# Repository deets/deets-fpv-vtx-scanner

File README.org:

* VTX Band Scanner

This little project provides a small scanner for the 39 VTX 
bands usually used (not the low L-band).

** Channel Table

| Frequency | Aomway | TBS Unify | Channel |
|-----------+--------+-----------+---------|
|      5645 | A4     | E4        |       0 |
|      5658 | E1     | R1        |       1 |
|      5665 | A3     | E3        |       2 |
|      5685 | A2     | E2        |       3 |
|      5695 | E2     | R2        |       4 |
|      5705 | A1     | E1        |       5 |
|      5725 | C1     | A8        |       6 |
|      5732 | E3     | R3        |       7 |
|      5733 | B1     | B1        |       8 |
|      5740 | D1     | F1        |       9 |
|      5745 | C2     | A7        |      10 |
|      5752 | B2     | B2        |      11 |
|      5760 | D2     | F2        |      12 |
|      5765 | C3     | A6        |      13 |
|      5769 | E4     | R4        |      14 |
|      5771 | B3     | B3        |      15 |
|      5780 | D3     | F3        |      16 |
|      5785 | C4     | A5        |      17 |
|      5790 | B4     | B4        |      18 |
|      5800 | D4     | F4        |      19 |
|      5805 | C5     | A4        |      20 |
|      5806 | E5     | R5        |      21 |
|      5809 | B5     | B5        |      22 |
|      5820 | D5     | F5        |      23 |
|      5825 | C6     | A3        |      24 |
|      5828 | B6     | B6        |      25 |
|      5840 | D6     | F6        |      26 |
|      5843 | E6     | R6        |      27 |
|      5845 | C7     | A2        |      28 |
|      5847 | B7     | B7        |      29 |
|      5860 | D7     | F7        |      30 |
|      5865 | C8     | A1        |      31 |
|      5866 | B8     | B8        |      32 |
|      5880 | D8     | F8        |      33 |
|      5880 | E7     | R7        |      34 |
|      5885 | A5     | E5        |      35 |
|      5905 | A6     | E6        |      36 |
|      5917 | E8     | R8        |      37 |
|      5925 | A7     | E7        |      38 |
|      5945 | A8     | E8        |      39 |
|-----------+--------+-----------+---------|

** RX5808 Connections

|-----+----------|
| Pin | Function |
|-----+----------|
|   1 | CH1/MOSI |
|   2 | CH2/CS   |
|   3 | CH3/CLK  |
|   4 | GND      |
|   5 | 5V       |
|   6 | RSSI     |
|   7 | Audio    |
|   8 | Video    |
|   9 | GND      |
|-----+----------|

** Developing on iOS

*** Dependencies

They are tracked in =Dependencies/Package.swift=.

Add a new =.package=-Declaration, refer it in
=.target(name="Dependencies")= and then run

#+begin_src bash
$ swift package update
$ rake xcodeproj
#+end_src

Then drag the new dependencies into Xcode.

[[https://github.com/apple/swift-package-manager/blob/master/Documentation/PackageDescriptionV4.md][Some explanation about Package.swift]]

*** Core Bluetooth Notes

 - [[https://stackoverflow.com/questions/13286487/how-can-i-reconnect-to-device-after-disconnecting-in-core-bluetooth][Reconnecting BT peripheral.]]

** Credits and Acknowledegements

 - Icons made by [[https://www.flaticon.com/packs/interface/2][Chanut]] from [[https://www.flaticon.com/][Flaticon]] is licensed by [[http://creativecommons.org/licenses/by/3.0/http://creativecommons.org/licenses/by/3.0/][CC 3.0 BY]]

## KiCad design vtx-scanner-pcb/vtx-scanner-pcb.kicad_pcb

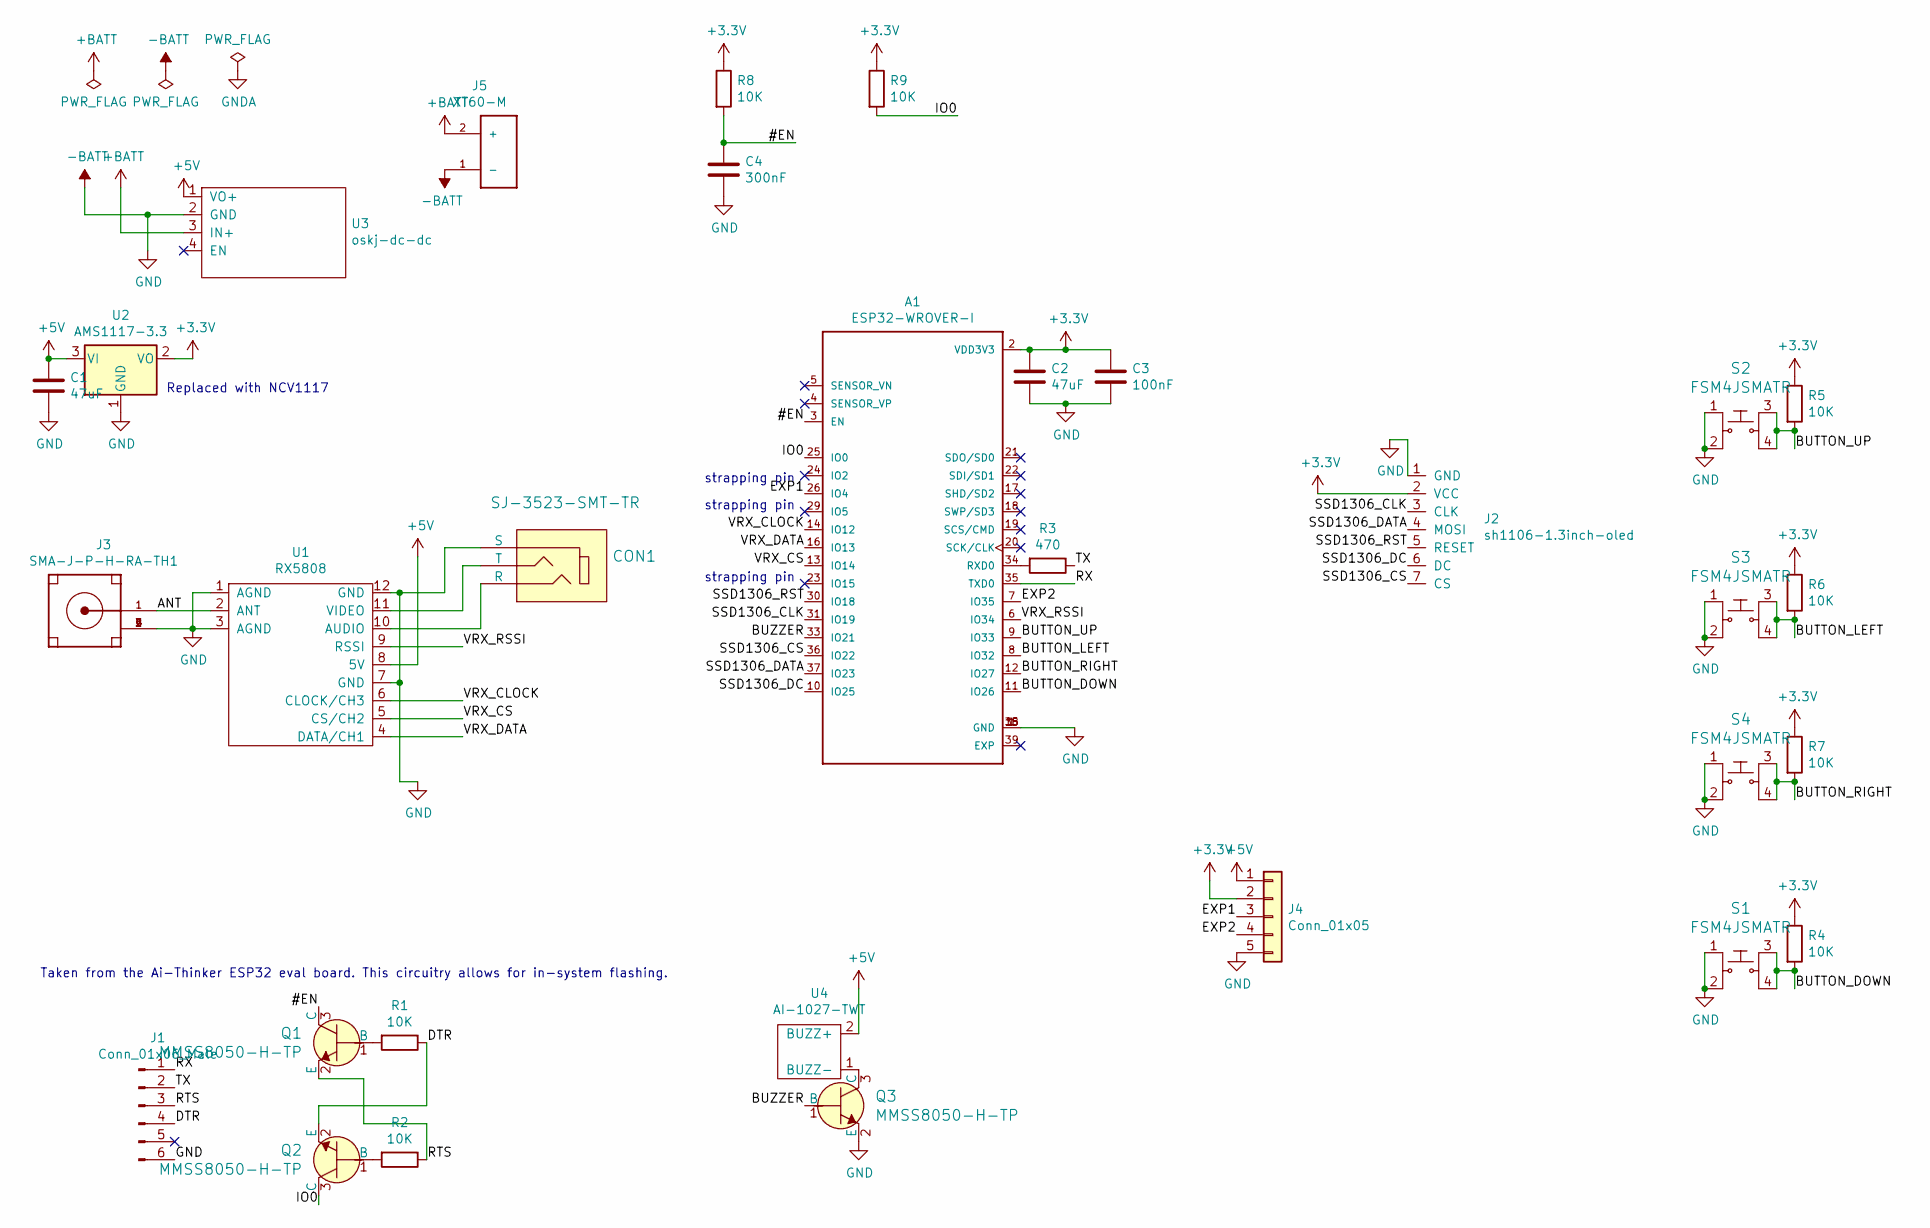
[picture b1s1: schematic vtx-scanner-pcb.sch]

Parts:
A1: ESP32-WROVER-I; XCVR_ESP32-WROVER-I
C1, C2: 47uF; CP_Elec_5x5.8
C3: 100nF; C_0805_2012Metric_Pad1.15x1.40mm_HandSolder
C4: 300nF; C_0805_2012Metric_Pad1.15x1.40mm_HandSolder
CON1: SJ-3523-SMT-TR; Switch_Slide_11.6x4mm_SJ-3523-SMT; MPN SJ-3523-SMT-TR; Digi-Key_PN CP-3523SJCT-ND
J1: Conn_01x06_Male; PinHeader_1x06_P2.54mm_Vertical
J2: sh1106-1.3inch-oled
J3: SMA-J-P-H-RA-TH1; SAMTEC_SMA-J-P-H-RA-TH1
J4: Conn_01x05; JST_PH_S5B-PH-K_1x05_P2.00mm_Horizontal
J5: XT60-M; AMASS_XT60-M-SIDE-MOUNT
Q1, Q2, Q3: MMSS8050-H-TP; SOT-23-3; MPN MMSS8050-H-TP; Digi-Key_PN MMSS8050-H-TPMSCT-ND
R1, R2, R4, R5, R6, R7, R8, R9: 10K; R_1206_3216Metric_Pad1.42x1.75mm_HandSolder
R3: 470; R_1206_3216Metric_Pad1.42x1.75mm_HandSolder
S1, S2, S3, S4: FSM4JSMATR; Switch_Tactile_SMD_6x6mm; MPN FSM4JSMATR; Digi-Key_PN 450-1759-1-ND
U1: RX5808
U2: AMS1117-3.3; SOT-223-3_TabPin2
U3: oskj-dc-dc
U4: AI-1027-TWT

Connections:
+3V3: A1.2 (VDD3V3), C2.1, C3.1, J2.2 (VCC), J4.2, R4.1, R5.1, R6.1, R7.1, R8.1, R9.1, U2.2 (VO)
+5V: C1.1, J4.1, U1.8 (5V), U2.3 (VI), U3.1 (VO+), U4.2 (BUZZ+)
+BATT: J5.2 (+), U3.3 (IN+)
-BATT: A1.1 (GND), A1.15 (GND), A1.38 (GND), C1.2, C2.2, C3.2, C4.2, CON1.1 (S), J1.6, J2.1 (GND), J3.2 (GND), J3.3 (GND), J3.4 (GND), J3.5 (GND), J4.5, J5.1 (-), Q3.2 (E), S1.1, S1.2, S2.1, S2.2, S3.1, S3.2, S4.1, S4.2, U1.1 (AGND), U1.3 (AGND), U1.7 (GND), U1.12 (GND), U2.1 (GND), U3.2 (GND)
/#EN: A1.3 (EN), C4.1, Q1.3 (C), R8.2
/ANT: J3.1 (SIGNAL), U1.2 (ANT)
/BUTTON_DOWN: A1.11 (IO26), R4.2, S1.3, S1.4
/BUTTON_LEFT: A1.8 (IO32), R6.2, S3.3, S3.4
/BUTTON_RIGHT: A1.12 (IO27), R7.2, S4.3, S4.4
/BUTTON_UP: A1.9 (IO33), R5.2, S2.3, S2.4
/BUZZER: A1.33 (IO21), Q3.1 (B)
/DTR: J1.4, Q2.2 (E), R1.1
/EXP1: A1.26 (IO4), J4.3
/EXP2: A1.7 (IO35), J4.4
/IO0: A1.25 (IO0), Q2.3 (C), R9.2
/RTS: J1.3, Q1.2 (E), R2.1
/RX: A1.35 (TXD0), J1.1
/SSD1306_CLK: A1.31 (IO19), J2.3 (CLK)
/SSD1306_CS: A1.36 (IO22), J2.7 (CS)
/SSD1306_DATA: A1.37 (IO23), J2.4 (MOSI)
/SSD1306_DC: A1.10 (IO25), J2.6 (DC)
/SSD1306_RST: A1.30 (IO18), J2.5 (RESET)
/TX: J1.2, R3.1
/VRX_CLOCK: A1.14 (IO12), U1.6 (CLOCK/CH3)
/VRX_CS: A1.13 (IO14), U1.5 (CS/CH2)
/VRX_DATA: A1.16 (IO13), U1.4 (DATA/CH1)
/VRX_RSSI: A1.6 (IO34), U1.9 (RSSI)
unnamed: A1.34 (RXD0), R3.2
unnamed: CON1.2 (T), U1.11 (VIDEO)
unnamed: CON1.3 (R), U1.10 (AUDIO)
unnamed: Q1.1 (B), R1.2
unnamed: Q2.1 (B), R2.2
unnamed: Q3.3 (C), U4.1 (BUZZ-)

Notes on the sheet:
Taken from the Ai-Thinker ESP32 eval board. This circuitry allows for in-system flashing.
strapping pin
Replaced with NCV1117

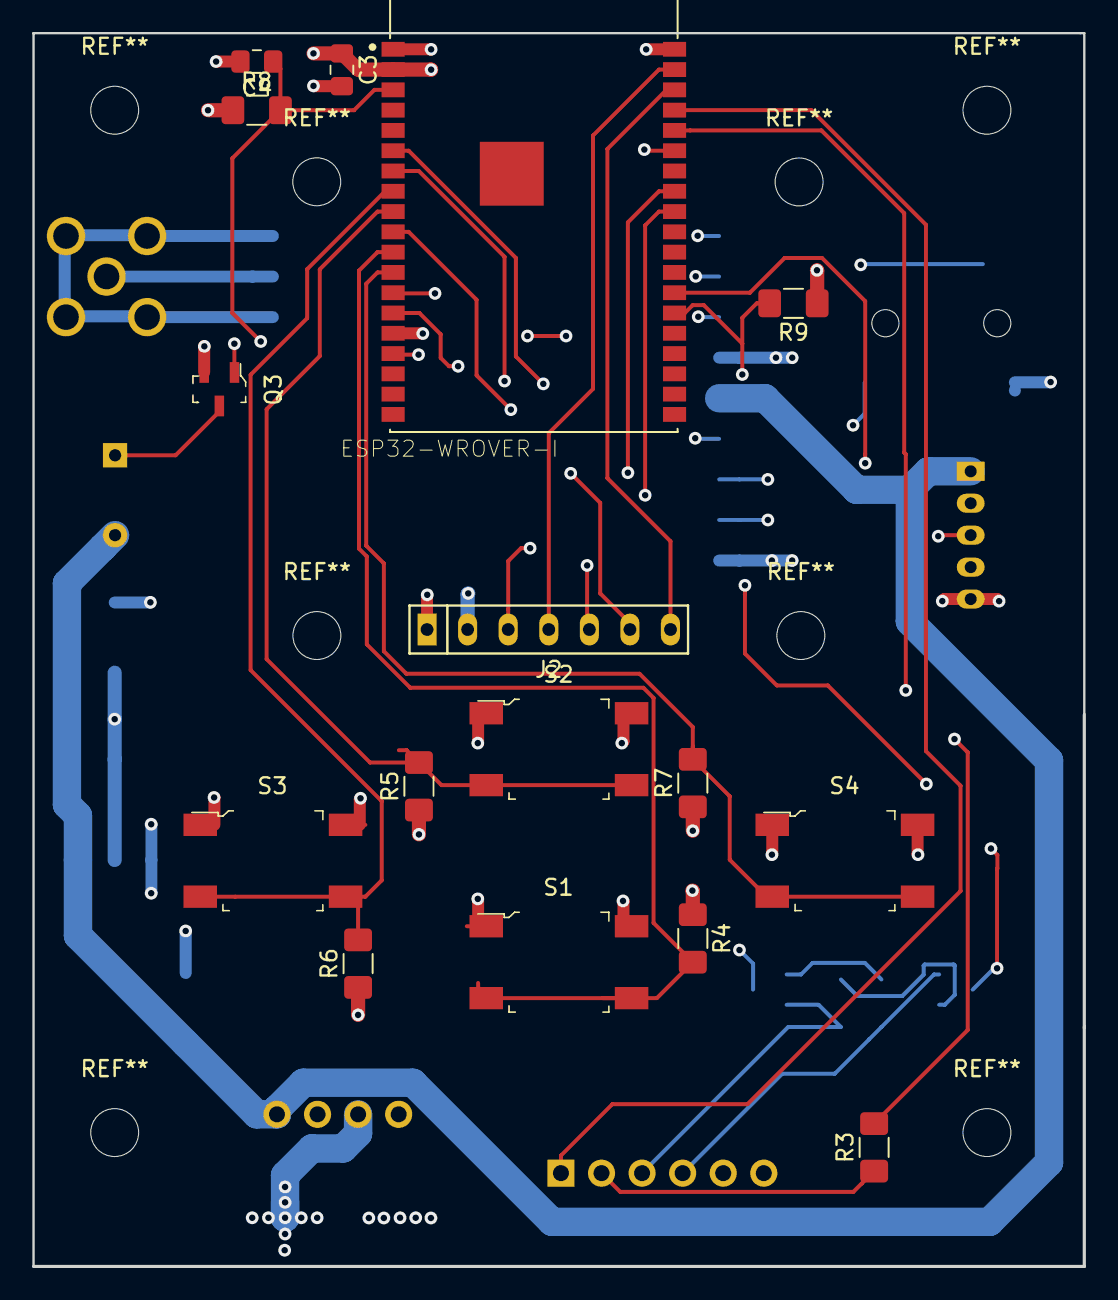
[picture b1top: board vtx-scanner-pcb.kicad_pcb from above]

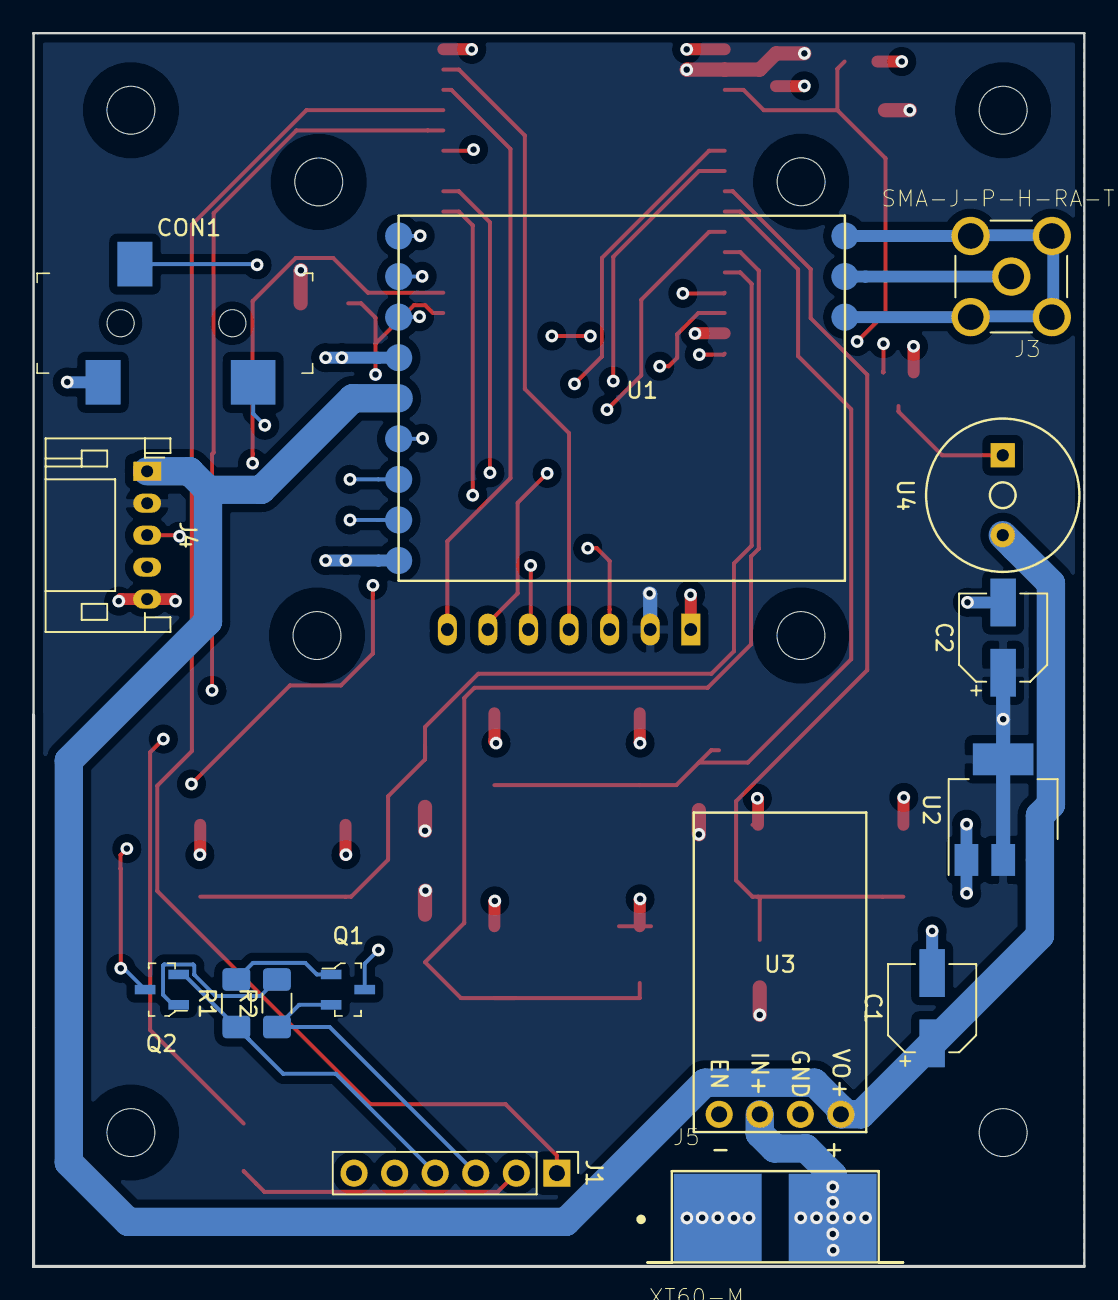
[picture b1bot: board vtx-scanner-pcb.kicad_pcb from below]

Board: 4 copper layers, 65.8 x 77.2 mm, 31 parts (15 on the bottom side), 33 nets.

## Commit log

2018-11-01 Initial build of spi server example works
2018-11-01 There is *something* to see on the display.
2018-11-01 Choose pin that works
2018-11-01 Lower SPI speed, might be reverted
2018-11-03 Cleanup license commits
2018-11-03 Implement set pixel method
2018-11-03 read analog pin
2018-11-04 Reworked the whole display stuff to be in its own files
    This means I can later extract it into a nice library
2018-11-04 Refactored starscroller into own sources
    Not needed in the near future I guess, but I like it too
    much to throw it away.
2018-11-04 Utility-Scripts
2018-11-04 Draw vertical lines, one per channel
2018-11-04 Read ADC with background task
2018-11-04 Use notifications to update display on-demand
2018-11-04 Drive channel selection via SPI
2018-11-04 Aomway frequency table
2018-11-05 Reworked RTC code into own source files
2018-11-05 Calculate the register value from a frequency
    This makes looking up the associated channel name
    easier in the future
2018-11-05 Converted frame-format to "normal" pixel alignment style
2018-11-06 Implement Sprites
2018-11-06 Implement font rendering
2018-11-07 Rewrite font-generator to be proper
2018-11-07 Add sprite generator based on PNGs with alpha channel
2018-11-07 Move diezface about
2018-11-07 Correct spelling error
2018-11-07 Experiment with GPIO ISR. Works on BOOT pin. Not on pin 4 :(
2018-11-13 Pull out channel display into own source files
    Also render with adaptive min/max
2018-11-13 Add cursor
2018-11-25 Place cursor on bottom
2018-11-25 Fill the rows
2018-11-25 Incorporate VTX info including legalness of channels w/o HAM
2018-11-25 Add TBS Unify Manual
2018-11-25 Add aomway channel names
2018-11-25 Updated docs
2018-11-26 Add table for channels and frequences
2018-12-15 Step left and right with GPIO 0 and 17
2018-12-15 Increase BPS for faster flashing
2018-12-15 Debounce buttons (globally for now)
2018-12-15 Start playing with a new font
2019-02-04 Cleanup: remove cruft from original example
2019-02-04 Adapted *.sh to work on mac and linux
2019-02-04 Rework to model app-state explicitly
2019-02-04 Use newer SDK
2019-02-04 Updgrade SDK config to 3.1.2
2019-02-04 Transplanted ble_counter example into my code
2019-02-04 Better setup/doc for ADC channel
2019-02-05 No core-dump and no restart after failure
2019-02-05 Most basic addition of another characteristic
    This still is buggy, as it relies on the first characteristic
    to be always subscribed - otherwise no updates come through.
2019-02-05 Converted ble.c to c++ and only notify the actual changes
2019-02-08 Document rx5808 module
2019-02-09 Use correct variable...
2019-02-09 Support setting cursor over BLE
2019-02-09 Migrate main to C++
2019-02-09 Remove unused resources
2019-02-09 Migrate to python 3.7
2019-02-10 Fix building for mac
2019-02-10 First iteration of splash screen
2019-02-10 Finishing touches on splash screen
2019-02-10 Migrated scanner to Mode-class
2019-02-10 Restore button channel selection
2019-02-10 Enable mode to delegate to another mode.
    This is probably only useful for the splash-screen, but ..
2019-02-10 Introduce current mode over BLE and allow it to change
    This is not really ideal, the lambda is a bit ugly. But
    it seems to work for now.
2019-02-12 Introduce storage in NVS
2019-02-12 Add max rssi tracking and notification
2019-02-13 Introduce basic laptimer
2019-02-13 Laptimer actually aquires data
2019-02-13 Basic lap-timing working
2019-02-13 Laptime printing works
2019-02-13 Better visualisation
2019-02-14 buzzer working, plus enhanced laptimer display
2019-02-14 Add cooldown period
2019-02-16 Start working on schematic/PCB
2019-02-17 Remove old library
2019-02-17 Lots of progress with the schematic and a bit of the PCB
2019-02-17 Added comment for future update
2019-03-02 Refactored IO setup
2019-03-02 Introduce mode manager to encapsulate mode switching
2019-03-02 Switch mode
    It appears we need more bounce-time as othewise too fast switching
    crashes the system.
    I presume this is due accessing SPI at the same time from two tasks.
    This obviously shouldn't happen.
2019-03-02 Per-button debouncing
2019-03-03 Advertising our service id
2019-03-03 Add iOS app
2019-03-03 First ScannerView implementation
2019-03-03 First characteristic notification
2019-03-08 Add dependencies
2019-03-08 Restructured a bit so that Signals start playing a role
2019-03-08 Use BinUtils to unpack binary data
2019-03-08 Use unordered map, because I think it's better..
2019-03-08 Propagate signals to actual value updates
2019-03-09 Rework signals to be emitted in main-thread
2019-03-09 Fix bug in BLE code that wouldn't allow for actual reads
2019-03-09 Introduce max RSSI property
2019-03-09 Add RTC6715 datasheet
2019-03-10 Add SwiftSVG as dependency and make a first mock-use of it
2019-03-10 Use mode in laptimer view
2019-03-20 Add random data view
2019-03-20 Started laying out PCB
2019-03-20 First stab at transmitting laptimer data
2019-03-20 Read laptimer data periodically
2019-03-24 Add utility script
2019-03-24 Move more code to C++
2019-03-24 Fix bug in io ISR
2019-03-24 First stab at transmitting actual laptimer RSSI value
    It works, but currently too many values are being transmitted.
2019-03-24 Now render from oldest (left) to newest (right)
2019-03-24 Only send the right amount of laptime data, and forget about the count
2019-04-13 Reworked build/flash/monitor scripts to be smarter and have common base script
2019-04-13 Latest version of deets kicad lib
2019-04-13 Fully laid-out 4 layer PCB, the first!
2019-04-13 Re-organised a couple of power lines
2019-05-30 Add latest library
2019-05-30 Continue re-layouting
2019-05-31 re-layout finished
2019-05-31 Gerber ZIP creation tool
2019-05-31 More PCB work
2019-06-15 ios stuff
2019-06-22 Pass in SPI speed
2019-06-22 Add ESPBAUD to common.sh
2019-06-22 Buzzer now takes pin as setup argument
2019-06-22 Remap buttons to PCB
2019-06-22 Add missing pullups and capacitor for #EN
2019-06-22 Fixed rx5808
2019-06-22 Begin componentization of code
2019-06-23 Moved display DC to IO25 as IO15 is a strapping pin
2019-06-23 Use fixed display DC pin and updated esp32components module
2019-06-23 Use BTSTACK
2019-07-06 Migrated to U8g2. And SH1106.
2019-07-06 Minor update in schematic
2019-07-06 First order of PCB documents
2019-07-07 Better font-handling, introduction of small font
2019-07-07 Some cleanup
2019-07-13 Reworked PCB
    - missing pullups IO0/EN
    - added capacitors for EN
    - clearance around mounting holes
    - better 2.4GHz antenna placement
    - correct rx5808 size
2019-07-14 Reworked gerber processing
2019-07-14 Removed a few superfluous track pieces
2019-07-14 Second PCB order
2019-07-14 Reworked periodic to be esp_timer_t based
2019-07-14 Add some explanation to prevent making a mistake in the future
    again.
2019-07-14 Cleaned up laptimer in preparation of re-implementation of trigger strategy
2019-07-14 Introduce basic settings mode
    Currently faked, but switching from/to settings works
2019-07-17 Dynamic core computation
2019-07-17 Adapted to newer compiler/SDK version
2019-07-17 Updated config to work with latest SDK
2019-07-22 Fix bug in last_rssi size calculation
2019-07-22 Remove superfluous pragma
2019-07-22 Reworked RTC6715 to become class and guard SPI with mutex
2019-07-22 Fix bug in which last_rssi was notified way too often in laptimer
2019-07-23 Fixed a problem with the wrapped data copying
2019-07-23 Moved back to SDK 3.2.2 release
2019-07-23 Submodule: update to the latest esp32components
2019-07-24 Fix the most stupid bug ever, that wasted solid 4h for me
2019-07-24 Re-enable buzzer
2019-07-24 First stab at laptime strategy
2019-07-24 Tune peak detection, communicate state changes via callback and queue
2019-07-24 Migrated finnaly BLE to class
2019-07-24 Introduce lap time tracking in preparation for offering these over BLE
2019-07-25 Communicate laptime events over BLE
2019-07-25 Enhance data copying
2019-07-25 Display current and past laptimes
2019-09-01 Introduce cooldown period
2019-09-01 Use left button to reset laptimes
2019-09-01 Fix filename case bug
2019-09-01 Migrated to cocoa pods
2019-09-02 Reworked ScannerView to just take signals instead of observing delegates
2019-09-21 Some VTX scanner stuff
2019-09-22 Add some comment
2019-09-22 Fix compilation warning
2019-09-22 Start enumerating settings
2019-09-23 Choose font with actual characters in it
2019-09-23 Show value for currently changed setting
2019-09-27 Add unit to settings display
2019-09-27 Generalised storage and restoring, works for peak length now, too
2019-09-27 Generalised NVS calls for different types
2019-09-27 Removed code smell - BackSetting shouldn't be global
2019-10-05 Add macOS-app while waiting for SwiftUI to become available
2019-10-06 Add table view that is model driven to star playing around with listed vtx gizmos
2019-10-06 We can now resize the window again
2019-10-06 Figured out how to use the actual NSTableCellView instead of creating my own
2019-10-12 Introduce VTX scanner list
2019-10-12 Use dependency injection to set scanner-list
2019-10-21 More configuration options for laptimer
2019-10-21 Small refactoring
2019-10-22 Introduce first Cocoa variant of VTXDataLogger
2019-10-22 Display ScanView
2019-10-22 Toggle tabs based on VTX mode
2019-10-22 Introduce LaptimerView and display values/second in it
2019-10-22 Increase laptimer task priority
2019-10-22 Add logging for time-delta every 1000 steps to gauge task scheduling
2019-10-22 Add rendering of sampled waveform
2019-10-22 Add capturing of rssi values
2019-10-22 Fix race-condition where queue was not yet existing when task was started already
2019-10-23 Trigger mode change through tabs
2019-10-23 Write gain values
    to no effect, but it's possible...
2019-10-23 Buzzer configurable
2019-10-24 Fix bug that prevented window from being shown
2019-10-24 Introduce current RSSI value display
2019-10-29 Add first attempt at data exploration
2019-10-30 Add filtering and display of several filtered data sets
2019-10-30 Add a couple of runs
2019-10-30 Add max RSSI line
2019-10-30 Automagically adapt retained sample size to reduce rendering time
2019-10-30 Tune ADC as seen in
    https://github.com/AlessandroAU/Chorus32-ESP32LapTimer/
2019-10-30 Add bit-filter and threshold based laptime determination
2019-10-30 Implement strategy following the results from the data logging
    This is much simplified, just a > max-rssi * % approach.
2019-10-30 Try other dataset
2019-10-31 Introduce concepts of laps / race, including special buzzing tone at the end.
2019-11-16 Fix small layout-bug
2019-11-16 Introduce time-stamp-tracking
2019-11-17 Convert to rx-based approach, with selection of scanner in list-view
2019-11-17 Work on menu, quit on window closing
2019-11-20 Use custom view to render scanner in table view
2019-11-20 Also introduce row-view, that seems to be the ticket for better rendering
2019-11-21 Highlighting of selected scanner based on palette and delegated to row view
2019-11-21 Become more robust by reconnecting to disconnected peripherals
2019-11-22 Allow to fake laps with right-press
2019-11-22 Introduce flyby and started
